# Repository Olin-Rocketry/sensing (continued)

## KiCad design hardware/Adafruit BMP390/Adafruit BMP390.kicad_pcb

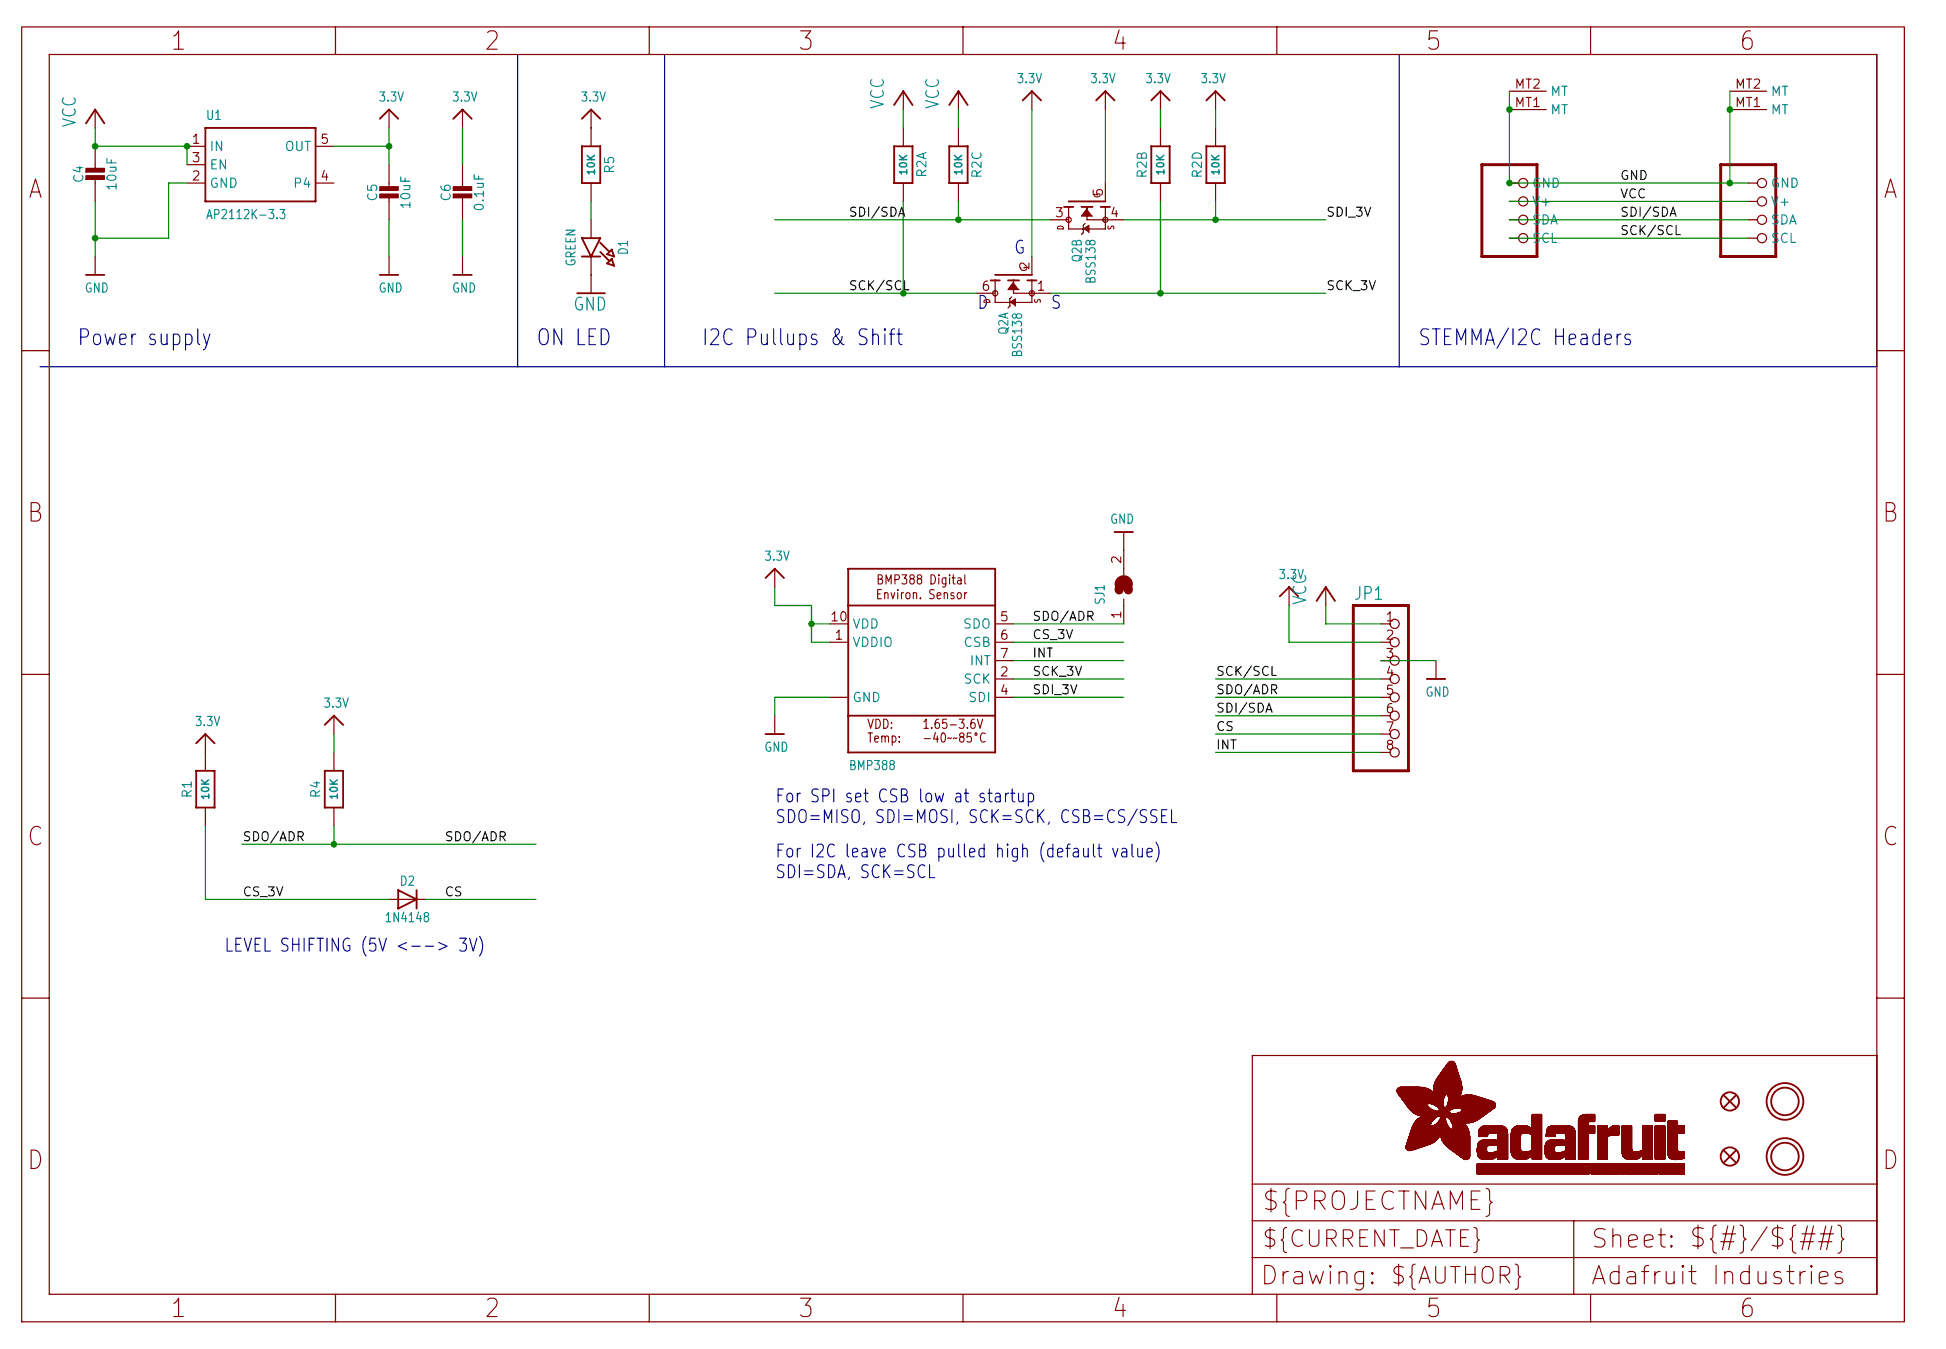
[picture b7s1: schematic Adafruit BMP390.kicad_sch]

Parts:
C4, C5: 10uF; 0805-NO
C6: 0.1uF; 0603-NO
CONN3, CONN4: STEMMA_I2C_QT; JST_SH4
D1: GREEN; CHIPLED_0603_NOOUTLINE
D2: 1N4148; SOD-323
FID3, FID4: FIDUCIAL_1MM
IC1: BMP388
JP1: HEADER-1X870MIL; 1X08_ROUND_70
Q2: BSS138; SOT363
R1, R4, R5: 10K; 0603-NO
R2: 10K; RESPACK_4X0603
SJ1: SOLDERJUMPER; SOLDERJUMPER_ARROW_NOPASTE
U1: AP2112K-3.3; SOT23-5
U$40, U$41: MOUNTINGHOLE2.5; MOUNTINGHOLE_2.5_PLATED

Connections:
3.3V: C5.1, C6.1, IC1.1 (VDDIO), IC1.10 (VDD), JP1.2, Q2.2 (G), Q2.5 (G), R1.2, R2.2 (1), R2.4 (1), R4.2, R5.1, U1.5 (OUT)
CS: D2.C, JP1.7
CS_3V: D2.A, IC1.6 (CSB), R1.1
GND: C4.2, C5.2, C6.2, CONN3.1 (GND), CONN3.MT1 (MT), CONN3.MT2 (MT), CONN4.1 (GND), CONN4.MT1 (MT), CONN4.MT2 (MT), D1.C, IC1.3 (GND), IC1.8 (GND), IC1.9 (GND), JP1.3, SJ1.2, U1.2 (GND)
INT: IC1.7 (INT), JP1.8
unnamed: D1.A, R5.2
SCK/SCL: CONN3.4 (SCL), CONN4.4 (SCL), JP1.4, Q2.6 (D), R2.8 (2)
SCK_3V: IC1.2 (SCK), Q2.1 (S), R2.7 (2)
SDI/SDA: CONN3.3 (SDA), CONN4.3 (SDA), JP1.6, Q2.3 (D), R2.6 (2)
SDI_3V: IC1.4 (SDI), Q2.4 (S), R2.5 (2)
SDO/ADR: IC1.5 (SDO), JP1.5, R4.1, SJ1.1
VCC: C4.1, CONN3.2 (V+), CONN4.2 (V+), JP1.1, R2.1, R2.3 (1), U1.1 (IN), U1.3 (EN)

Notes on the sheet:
For SPI set CSB low at startup SDO=MISO, SDI=MOSI, SCK=SCK, CSB=CS/SSEL
ON LED
LEVEL SHIFTING (5V <--> 3V)
I2C Pullups & Shift
For I2C leave CSB pulled high (default value) SDI=SDA, SCK=SCL
STEMMA/I2C Headers
Power supply

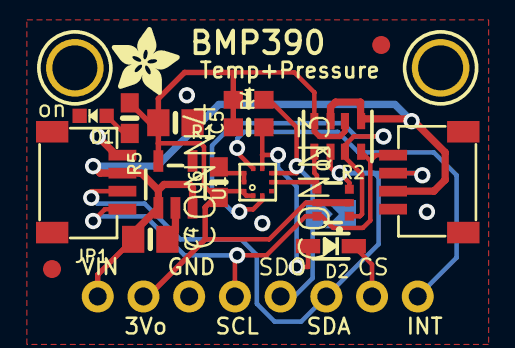
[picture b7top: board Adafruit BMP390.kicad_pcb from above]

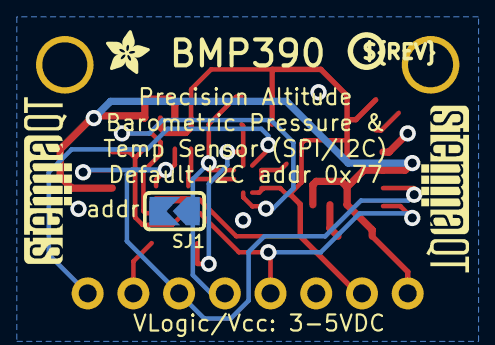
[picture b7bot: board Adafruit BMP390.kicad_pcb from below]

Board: 2 copper layers, 25 parts (5 on the bottom side), 12 nets.

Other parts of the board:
U$2: ADAFRUIT_2.5MM
U$46: ADAFRUIT_3.5MM
U$47: PCBFEAT-REV-040
U$48, U$49: STEMMAQT

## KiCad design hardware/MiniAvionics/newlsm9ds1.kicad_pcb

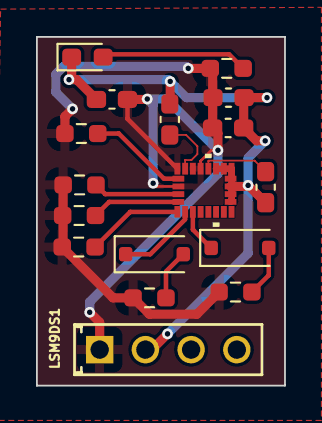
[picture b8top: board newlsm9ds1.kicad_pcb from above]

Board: 2 copper layers, 13.8 x 19.4 mm, 17 parts (0 on the bottom side), 13 nets.

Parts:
C1: 0.22uF; C_0603_1608Metric_Pad1.08x0.95mm_HandSolder
C2: 0.01uF; C_0603_1608Metric_Pad1.08x0.95mm_HandSolder
C3: 100nF; C_0603_1608Metric_Pad1.08x0.95mm_HandSolder
C4: 10uf; C_0603_1608Metric_Pad1.08x0.95mm_HandSolder
C6: 100uF; C_0603_1608Metric_Pad1.08x0.95mm_HandSolder
D1, D2: Diode; 1N4148W
D3: LED; LED_0603_1608Metric_Pad1.05x0.95mm_HandSolder
IC1: LSM9DS1; lsm9ds1TR
J1: 826629-4; CON4_1X4_P100UM_HDR2_TYC
R1, R2, R4, R5, R6, R7: 10k; R_0603_1608Metric_Pad0.98x0.95mm_HandSolder
R3: 10K; R_0603_1608Metric_Pad0.98x0.95mm_HandSolder

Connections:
3.3V: C3.1, C4.1, C6.1, IC1.1 (VDDIO), IC1.3 (VDDIO), IC1.22 (VDD), IC1.23 (VDD), J1.1, R1.1, R2.1, R3.1, R4.1, R5.1, R6.1, R7.1
/CS_A/G: D2.1 (A), IC1.7 (CS_A/G)
/CS_M: D1.1 (A), IC1.8 (CS_M)
/GND: C1.2, C2.2, C3.2, C4.2, C6.2, D3.1 (K), IC1.14 (RESERVED(GND)), IC1.15 (RESERVED(GND)), IC1.16 (RESERVED(GND)), IC1.17 (RESERVED(GND)), IC1.18 (RESERVED(GND)), IC1.19 (GND), IC1.20 (GND), J1.2
/SDO_AG: IC1.5 (SDO_A/G), R1.2
/SDO_M: IC1.6 (SDO_M), R7.2
unnamed: D1.2 (C), R4.2
unnamed: D2.2 (C), R5.2
unnamed: D3.2 (A), R3.2
unnamed: C1.1, IC1.24 (C1)
unnamed: C2.1, IC1.21 (CAP)
SDA: IC1.2 (SCL/SPC), R6.2
SDO: IC1.4 (SDA/SDI/SDO), R2.2

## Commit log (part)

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2022-11-01 added DSPI
2022-11-01 Battery management
2022-11-10 Battery manangement
2022-11-17 File structure update
2022-11-18 Power updates
2022-11-18 Changed file structure
2022-11-29 changed gitignore
2022-11-29 Add edited board 4 and main prism teensy schematics
2022-11-30 Add voltage divider for measuring battery
2022-11-30 Power board changes
2022-12-06 Removed files
2022-12-06 Add buzzer and take out 2nd SPI
2022-12-06 add pcb templates
2022-12-07 IO board
2022-12-08 changed resistor values on IO
2022-12-09 Add footprints to resistors and LEDs
2023-02-03 add basic OOP demo
2023-02-06 add new arm switches
2023-02-11 Reverse Current
2023-02-15 Added EAST outline versions
2023-02-22 Revise PCB outlines with SD clip and new headers.
2023-02-22 Add GPS EAST
2023-02-22 Add GPS symbol and EAST PCB outline.
2023-02-22 Add .pretty for GPS
2023-02-22 Add GPS PCB
2023-02-22 Add GPS project to facilitate future reference.
2023-02-23 Merge
2023-02-23 work on PRISM io
2023-02-24 Update east gps layout
2023-02-25 Add altimeter files
2023-02-25 Add altimeter to footprint
2023-02-25 Edit footprint layout and resistor sizes
2023-02-25 Add east teensy footprint
2023-02-25 Change teensy serial labeling
2023-02-25 Edit schematic
2023-02-26 Update east communication and layout
2023-02-26 Update pin connections
2023-02-26 fixed some footprints on PRISM IO
2023-02-26 Add connector layout to PCB DXFs
2023-02-27 add footprint for diode
2023-02-28 Complete PRISM Teensy layout
2023-02-28 Switch connector pin order on IO
2023-02-28 Relocate USB-micro on main Teensy
2023-02-28 Completed EAST Teensy board, confused at GPS board
2023-03-01 Change gps footprint
2023-03-01 Edit layout of board 4
2023-03-01 Update EAST connectors
2023-03-03 Rough layout of main teensy board
2023-03-04 Add rough layout arrangement
2023-03-04 Final PRISM Teensy Layout
2023-03-04 Add final traces
2023-03-04 update core IO with minor changes
2023-03-04 new dxf for prism io
2023-03-05 add cad models
2023-03-05 Add schottcky diodes to main teensy
2023-03-05 logos
2023-03-06 io layout
2023-03-06 power routing
2023-03-06 finished CORE IO layout
2023-03-06 testing JLC order
2023-03-06 add mounting holes and update resistor size
2023-03-07 add plated holes to both east boards
2023-03-07 Completed IO layout, added board 1 plated holes
2023-03-07 Board one changed resistor size
2023-03-07 change board 4 C size and GPS labels hided
2023-03-07 minor fixes
2023-03-08 fixed 90deg trace
2023-03-08 Edit for design rule check
2023-03-08 Fix CoreIO board
2023-03-08 add square silk screen for GPS
2023-03-08 Board one complete
2023-03-08 fix DRC errors on PRISM FC
2023-03-08 Encode and SD_Write Demo
2023-03-09 PRISM_IO gerbers
2023-03-09 EAST JLC files
2023-03-10 An attempt at a Data class
2023-03-14 Add Data class that compiles
2023-03-14 Create Radio class
2023-03-14 Add class constructors
2023-03-24 Changed neopixel footprint
2023-03-24 Add starter imu files
2023-03-25 Add initial IMU and altimeter
2023-03-29 add simple altitude model
2023-03-29 re structure the file system
2023-03-29 set up demo
2023-03-29 Add gps class
2023-03-29 Edit header import
2023-03-29 change led pin
2023-03-29 Fix IMUf file structure
2023-03-29 Add altimeter class
2023-03-29 Add sending to Radio class
2023-03-29 Fixed altimeter code
2023-03-29 Add global accel variables
2023-03-30 re names some files
2023-03-31 Add mask layer for altimeter pads
2023-03-31 header pins pads fixed
2023-03-31 Update imu for quaternions
2023-03-31 Changed neopixel on board 4
2023-03-31 re structure DATA class
2023-04-01 Add rotation to rocket frame
2023-04-01 Format Data class and add demo
2023-04-01 Debugging Data encoding
2023-04-01 pcb fixes
2023-04-01 add working SD class demo
2023-04-01 Finalize Data encoding and decoding.
2023-04-01 implemented file naming scheme
2023-04-02 fixed a few pcb silkscreen things
2023-04-02 remove data copy
2023-04-02 Add untested data integration
2023-04-02 Fixed decode, no more corruption
2023-04-02 Add radio testing code.
2023-04-02 Add begin method
2023-04-02 Fix Radio testing code compile errors.
2023-04-02 pcb ship version
2023-04-02 remove data class duplicate
2023-04-02 update Radio
2023-04-02 Fix Radio sending buffer size.
2023-04-05 Add testing code
2023-04-05 Add tester cpp files
2023-04-05 data naming fix
2023-04-05 Test data commit
2023-04-05 fix naming issues
2023-04-05 fix naming
2023-04-05 Added data to altimeter class
2023-04-05 Update IMU
2023-04-05 Update IMUfor individual testing
2023-04-05 Add data for testing imu
2023-04-07 Add data to main folder
2023-04-07 Uncomment data assignments in imu
2023-04-07 Add altimeter and data
2023-04-07 Fix Data class order, remove ino
2023-04-07 Convert altimeter to cpp
2023-04-08 Update altitude method name
2023-04-08 Update SDDecode for use with ground station
2023-04-08 Add untested gps
2023-04-08 Serial communication
2023-04-10 led code working
2023-04-10 Update gps class
2023-04-10 Integrate Teensy-to-Teensy comms
2023-04-10 Remove data inclusion from GPS
2023-04-10 Add east code
2023-04-10 Add ground station
2023-04-10 Add time testing
2023-04-11 Seperation
2023-04-12 Include altimeter in prism main
2023-04-12 Remove unnecessary include statements
2023-04-12 Remove unnecessary comment
2023-04-12 move LED class into main folder
2023-04-12 Serial
2023-04-12 removed LED stuff (will fix later)
2023-04-12 Add include for altimeter
2023-04-12 Serial 8 and 5 in prism main
2023-04-12 Add instuctions for changing macros variables
2023-04-12 Seperation Test
2023-04-12 made EAST board code changes
2023-04-12 CHange frequency of data sent over serial
2023-04-12 added debugging on GS
2023-04-12 test east serial sendpacket
2023-04-12 Change to only use serial5
2023-04-12 Add debug string for sending data
2023-04-13 got it working!!!!!!!!!!!!!
2023-04-13 minor changes
2023-04-14 Add config to speed up radio
2023-04-15 working code (no altimeter)
2023-04-15 Add starter flight code
2023-04-15 Update prism main code with case switch skeleton
2023-04-16 add voltage and continuity to packet
2023-04-17 tried to integrate GPS
    Adding GPS prevents the serial transfer from working at full speed.
2023-04-18 separation test
2023-04-18 add altitude
2023-04-19 working
2023-04-19 Remove unnecessary rotation to global frame
2023-04-19 Altimeter sampling rate quicker
2023-04-19 Speeding up altimeter
2023-04-19 fixed gps integration and changed gps status color
2023-04-19 Add flight code
2023-04-19 Include phases in data
2023-04-19 Change main deploy to have relative cutoff alt
2023-04-19 first kalman fix attempt
2023-04-19 got kalman working
2023-04-19 Add delay adjustment based on loop duration
2023-04-19 Finish Data debug statements
2023-04-19 Add debugging to imu and collapse sensor readings
2023-04-19 Finished debug printing over Serial
2023-04-21 working code
2023-04-22 Add log files
2023-04-22 flight ready
2023-04-22 add launch data
2023-04-22 add gs logs
2023-04-22 Flight logs from test
2023-04-23 add plotting
2023-10-09 Add diagmsg for altimeter
2023-10-09 Add diagmsg to altimeter startup
2023-10-09 Add diagmessage to imu
2023-10-09 Added setup diag message
2023-10-09 added diagmsg to gps
2023-10-09 Diagmsg error codes into gps
2023-10-09 add diagmsg gps to main
2023-10-09 changed packetsize in radio in east
2023-10-09 changed packetsize in radio on gs
2023-10-16 Remove extraneous chars
2023-10-16 Add missing parentheses
2023-10-18 Add debug without SD mode
2023-10-21 Debug PRISM startup pause
2023-10-21 Fix gps error code exponent
2023-10-21 Modify when gps struct sent to serial
2023-10-25 Add gps debugging
2023-10-25 Fix diagmsg inital value
2023-10-25 Fix error issues
2023-10-25 added reset for diag message to fix GPS bug
2023-10-26 replaced pyro trigger with no delay implementation - NEED TO TEST!!!!
2023-10-28 Finalize launch code
2023-11-13 added new PRISM rev
2023-11-16 added teensy 4.0 and new connector spec
2023-11-27 added footprint and symbol
2023-11-27 Adding symbol to kicad library
2023-11-27 add led
2023-11-27 added TMC2209
2023-11-29 added new IMU footprint + symbol
2023-11-29 new buzzer replaced
2023-11-29 moving GPS and Radio to main
2023-11-29 moved folders for libraries
2023-12-06 Added Parts
2023-12-06 Add log files and thrust test stand cals
2023-12-06 Change folder naming
2023-12-06 Did some organizing
2023-12-06 created new symbol and footprint for buzzer
2023-12-07 Kicad
2023-12-07 Add files via upload
    CON4_1X4_P100UM_HDR2_TYC is connector
2023-12-07 Add files via upload
    826629-4 is connector
2023-12-11 bmp390
    ff
2023-12-11 BMP 390 Schematic
2023-12-11 finished bmp
2023-12-13 fixing merge conflict
2024-01-01 Procrastinated PRISM commit
2024-01-02 Finalized PRISM schematic
2024-01-02 Fix some issues with PRISM FC schematic
2024-01-02 Finish PRISM FC schematic
2024-01-02 Fix file name issue
2024-01-02 Need to fix SD slot still
2024-01-03 Fix SD Detect error
2024-01-03 Final PRISM FC Board
2024-01-03 create new footprint
    created footprint for the smaller LSM9DS1 breakout board
2024-01-03 Add GPS PRISM FC layout, no wiring
2024-01-03 Final PRISM GPS Board
2024-01-04 update Core IO schematic and first layout concept
2024-01-07 fixed stepper wiring
2024-01-10 Finished stepper implementation
2024-01-10 Fix problem with 3V3 plane
2024-01-10 Fix silkscreen issue in PRISM FC
2024-01-10 Add grounded mount on FC
2024-01-10 Save backup of GS Radio before new layout
2024-01-10 New GS Radio board layout without wiring
2024-01-10 Finished GS Radio layout
2024-01-10 Add credits and aesthetics to GS Radio
2024-01-12 finished IO layout
2024-01-13 Add logo and switch displays to HSPI radio
2024-01-13 Add aesthetics to IO board
2024-01-13 Add JLC part numbers to FC
2024-01-14 Add big buzzer to FC
2024-01-14 Move resistors out of solder iron path
2024-01-14 Change IO pulldown resistors
2024-01-15 Push final mini avionics
2024-01-18 add battery holder cad
2024-01-19 add unscented demo
2024-01-19 add 7D version
2024-01-19 Changed capacitor
    Changed the large capacitor for the voltage regulator to reflect BOM
2024-01-23 Fixed GPS breakout schematic pin assignment and updated board to update traces
2024-01-25 Fixed Silkscreen and removed power plane
2024-01-25 Add voltage divider to measure battery voltage
    Added a voltage divider and connected it to one of the analog input pins of the ESP32 so we can actually measure the battery voltage
2024-01-25 Added 3.3V line and fixed analog routing issues on Teensy
2024-01-25 Forgot to save schematic from last push
2024-01-25 Updated Core IO connectors to match updated Teensy board and change stepper to 3.3V
2024-01-25 Final FC Board
2024-01-25 Move capacitor closer on Radio Board
2024-01-31 Production Main Avionics Boards
2024-01-31 Add Rev4 Codebase
2024-02-21 Updated Rev4 based on new changes to components
    Combined EAST and Prism. Updated IMU class with appropriate IMU. Added code for buzzer.
2024-02-23 implemented active aero model with UKF - working!!
2024-02-26 Update Radio Board
2024-03-11 Fixing some errors, still some left
2024-03-25 add cad
2024-03-27 add plastic bits and bobs
2024-03-27 Main Avionics Compiles!
    Removed double definition of float_u in radio and data encode classes
2024-04-07 battery holder cad
2024-04-10 battery mount cad
2024-04-15 Radio Class Fixes
    Mostly Fixed Radio Class, still having issues RF95
2024-04-16 LEDs work
2024-04-16 Something's wrong with sendRadio
2024-04-16 Fix radio crash error
2024-04-16 Working radio printing
2024-04-17 Nightly Push 4/17
2024-05-26 add groundstation radio files
2024-09-17 Add avionics onboarding template
2024-10-14 Add 10-28 flight data
2024-10-31 Changes up to discovery of Hardware issue
2024-12-26 Added Missing holes on CoreIO
2024-12-26 Fixed PRISM SD Card
2025-01-25 Continued Debugging
2025-01-26 fixed latch
2025-03-13 Add support for RFM69 Module
2025-03-29 Pushing all changes before rebase
2025-04-06 Certification Boards Schematics
2025-04-13 Add radio board rev2 files
2025-04-17 Add datasheets
2025-04-17 Add comments to cert avionics
2025-04-23 changed IMU read functions which allows setting values in the data class
2025-04-23 added Madgwick orientation esimation functionality for Euler angles
2025-04-24 some code organization
2025-05-04 Fixed issues with stepper class
